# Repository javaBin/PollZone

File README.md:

# Arduino

Configure your Arduino IDE with ESP8266 support: File -> Preferences, add `http://arduino.esp8266.com/stable/package_esp8266com_index.json` under *Additional Board Manager URLs*.

Open the Board Manager: Tools -> Board -> Board Manager and add the `esp8266` board. Current version: `2.2.0`

# BOM - Bill of materials

For 20 bokser:

* 20 x grønn knapper
* 20 x gule knapper
* 20 x røde knapper
* 6 blanke PCBer
* loddetinn
* 20 NodeMCU 
* 20 usb-kabler (kanskje lange, spør hilde)
* 20 ladere
* 80 x distanseskruer 2-3mm
* 80 x maskinskruer til distanseskruer
* 20 x micro-usb-kontakter
* 60 x 1k ohm motstander
* 60 x 120 ohm til blå led
* 60 x 150 ohm til gul led
* 60 x 150 ohm til rød led
* 60 x kondensator
* 240 sko "ca størrelse 15"
* ledninger 

# TODOs

## Box

Modifiser trekasse.
- Litt lavere
- Skjære ut små hull for "feste-tapper" i led-lysene
- USB-utgang på sidevegg
- Gravere inn logo
- plexiglass/akryl
- 3d-printe mounting-brackets for usb.
- Huske å legg panelet riktig vei slik at "svidde kanter" hanver på innsiden.

Avklaringer:
- 2.4GHz nett i spektrum
- Spør om det er strøm ved bordene

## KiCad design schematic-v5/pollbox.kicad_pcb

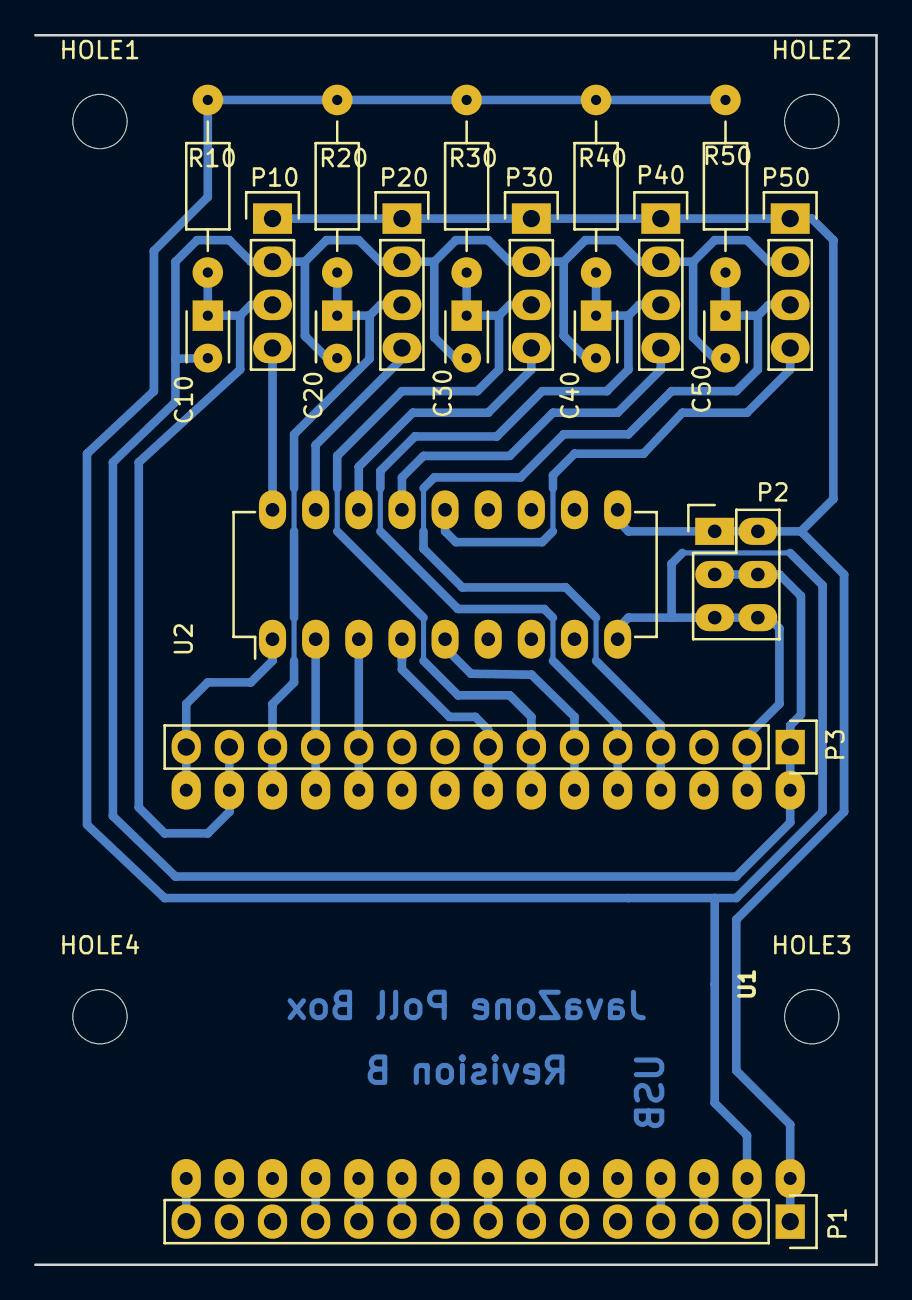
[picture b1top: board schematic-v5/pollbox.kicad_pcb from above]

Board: 2 copper layers, 49.5 x 72.4 mm, 24 parts (0 on the bottom side), 27 nets.

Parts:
C10, C20, C30, C40, C50: 100n; C_Disc_D3_P2.5
HOLE1: M1; MountingHole_3.2mm_M3
HOLE2: M2; MountingHole_3.2mm_M3
HOLE3: M4; MountingHole_3.2mm_M3
HOLE4: M3; MountingHole_3.2mm_M3
P1, P3: Pin_Header_Straight_1x15
P2: Power; Pin_Header_Straight_2x03
P10: SW_1; Pin_Header_Straight_1x04
P20: SW_2; Pin_Header_Straight_1x04
P30: SW_3; Pin_Header_Straight_1x04
P40: SW_4; Pin_Header_Straight_1x04
P50: SW_5; Pin_Header_Straight_1x04
R10, R20, R30, R40, R50: 10k; Resistor_Horizontal_RM10mm
U1: NodeMCU_1.0; NodeMCU
U2: ULN2803; DIP-18_W7.62mm_LongPads

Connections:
+3V3: C10.2, C20.2, C30.2, C40.2, C50.2, P2.3, P2.4, P3.1, P10.2, P20.2, P30.2, P40.2, P50.2, U1.30
+5V: P1.1, P2.1, P2.2, P10.1, P20.1, P30.1, P40.1, P50.1, U1.1, U2.10
/AD0: P1.15, U1.15
/CLK: P1.7, U1.7
/CMD: P1.9, U1.9
/EN: P1.4, U1.4
/LED_1: P3.15, U1.16, U2.1
/LED_1_OUT: P10.4, U2.18
/LED_2: P3.12, U1.19, U2.2
/LED_2_OUT: P20.4, U2.17
/LED_3: P3.11, U1.20, U2.3
/LED_3_OUT: P30.4, U2.16
/LED_4: P3.8, U1.23, U2.4
/LED_4_OUT: P40.4, U2.15
/LED_5: P3.6, U1.25, U2.5
/LED_5_OUT: P50.4, U2.14
/SD0: P1.8, U1.8
/SD1: P1.10, U1.10
/SD2: P1.11, U1.11
/SD3: P1.12, U1.12
/SWITCH_1: C10.1, P3.14, P10.3, R10.1, U1.17
/SWITCH_2: C20.1, P3.13, P20.3, R20.1, U1.18
/SWITCH_3: C30.1, P3.7, P30.3, R30.1, U1.24
/SWITCH_4: C40.1, P3.5, P40.3, R40.1, U1.26
/SWITCH_5: C50.1, P3.4, P50.3, R50.1, U1.27
/~RST: P1.3, U1.3
GND: P1.2, P2.5, P2.6, P3.2, R10.2, R20.2, R30.2, R40.2, R50.2, U1.2, U1.29, U2.9

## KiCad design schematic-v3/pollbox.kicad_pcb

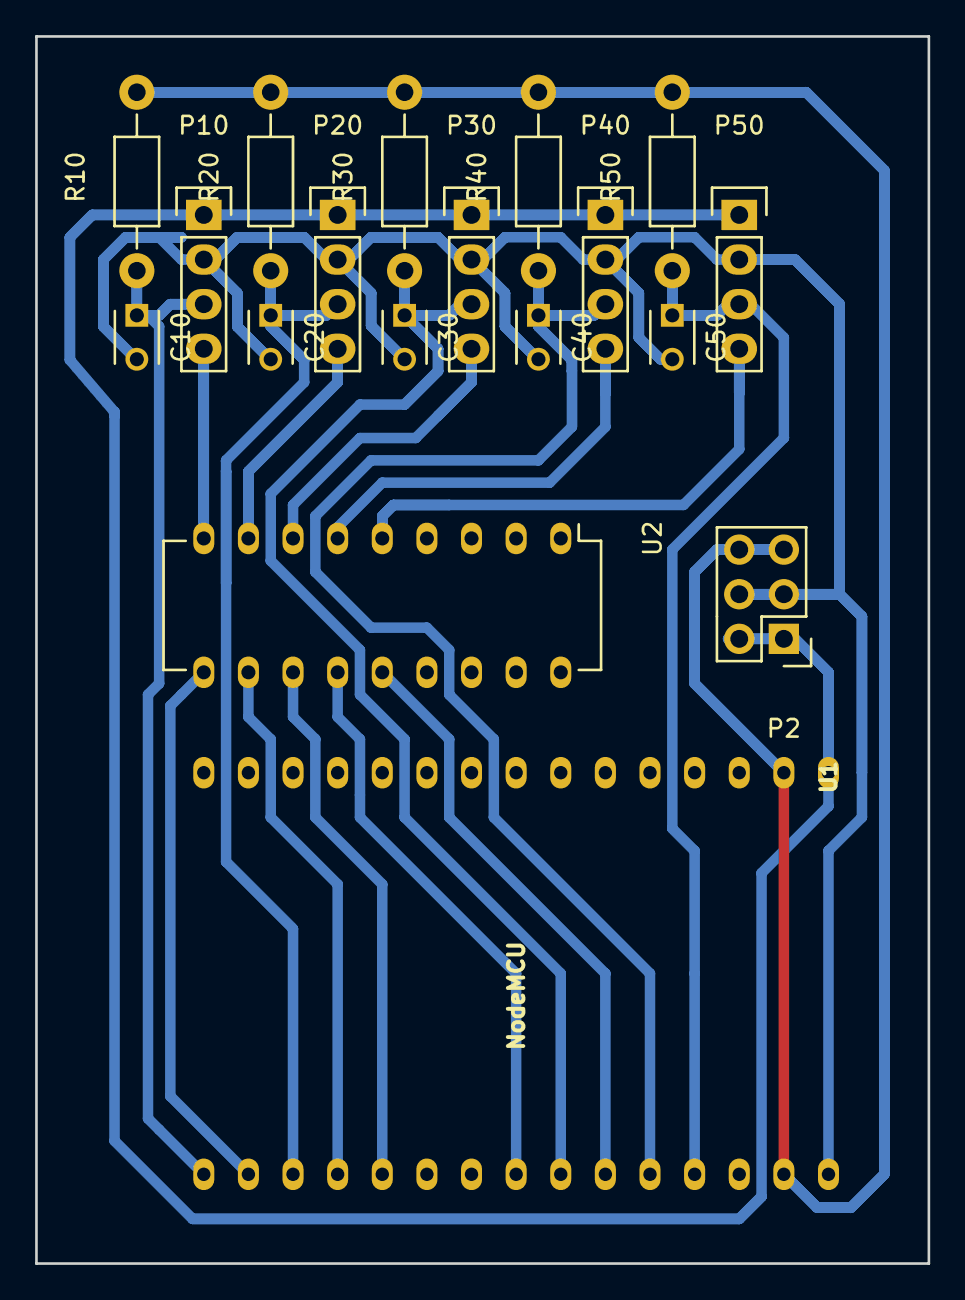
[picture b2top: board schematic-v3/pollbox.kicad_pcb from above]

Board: 2 copper layers, 50.8 x 69.8 mm, 18 parts (0 on the bottom side), 18 nets.

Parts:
C10, C20, C30, C40, C50: 100n; C_Disc_D3_P2.5
P2: CONN_02X03; Pin_Header_Straight_2x03
P10, P20, P30, P40, P50: CONN_01X04; Pin_Header_Straight_1x04
R10, R20, R30, R40, R50: 10k; Resistor_Horizontal_RM10mm
U1: NodeMCU; NodeMCU_oval_pads
U2: ULN2803; ULN2803_oval_pads

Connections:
+3V3: C10.2, C20.2, C30.2, C40.2, C50.2, P2.3, P2.4, P10.2, P20.2, P30.2, P40.2, P50.2, U1.30
+5V: P2.1, P2.2, P10.1, P20.1, P30.1, P40.1, P50.1, U1.1
/LED_1: P10.4, U2.9
/LED_2: P20.4, U2.8
/LED_3: P30.4, U2.7
/LED_4: P40.4, U2.6
/LED_5: P50.4, U2.5
/SWITCH_1: C10.1, P10.3, R10.1, U1.16
/SWITCH_2: C20.1, P20.3, R20.1, U1.18
/SWITCH_3: C30.1, P30.3, R30.1, U1.24
/SWITCH_4: C40.1, P40.3, R40.1, U1.26
/SWITCH_5: C50.1, P50.3, R50.1, U1.27
GND: P2.5, P2.6, R10.2, R20.2, R30.2, R40.2, R50.2, U1.2, U1.29
unnamed: U1.17, U2.10
unnamed: U1.19, U2.11
unnamed: U1.20, U2.12
unnamed: U1.23, U2.13
unnamed: U1.25, U2.14

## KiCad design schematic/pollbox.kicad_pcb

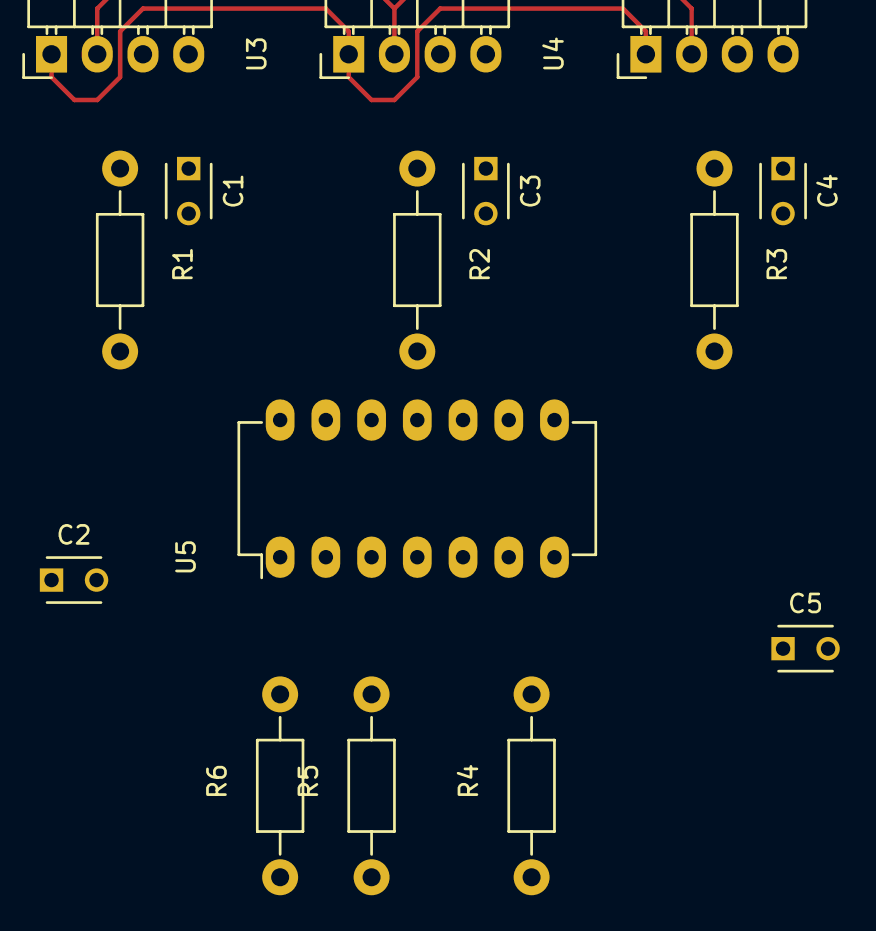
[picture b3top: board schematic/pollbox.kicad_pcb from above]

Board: 2 copper layers, 15 parts (0 on the bottom side), 12 nets.

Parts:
C1, C2, C3, C4, C5: 100n; C_Disc_D3_P2.5
R1, R2, R3: 10k; Resistor_Horizontal_RM10mm
R4, R5, R6: 1k; Resistor_Horizontal_RM10mm
U2, U3, U4: BIG_BUTTON; Pin_Header_Angled_1x04
U5: LM3046; DIP-14_W7.62mm_LongPads

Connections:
+3V3: C1.2, C3.2, C4.2, C5.2, U2.1, U3.1, U4.1
+5V: C2.1, U2.2, U3.2, U4.2
GND: C2.2, C5.1, R1.2, R2.2, R3.2, U5.7, U5.10, U5.13
unnamed: C1.1, R1.1, U2.4
unnamed: C3.1, R2.1, U3.4
unnamed: C4.1, R3.1, U4.4
unnamed: R4.2, U5.6
unnamed: R5.2, U5.9
unnamed: R6.2, U5.12
unnamed: U2.3, U5.14
unnamed: U3.3, U5.11
unnamed: U4.3, U5.8

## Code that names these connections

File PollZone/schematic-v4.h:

namespace schematic {

static const int AD0 = 0;
static const int LED_1 = 5;
static const int LED_2 = 0;
static const int LED_3 = 2;
static const int LED_4 = 14;
static const int LED_5 = 13;
static const int SD2 = 9;
static const int SD3 = 10;
static const int SWITCH_1 = 16;
static const int SWITCH_2 = 4;
static const int SWITCH_3 = 12;
static const int SWITCH_4 = 15;
static const int SWITCH_5 = 3;

} // namespace schematic

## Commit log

2015-12-01 o Adding schematic.
2015-12-01 added code for three buttons and reset button
2015-12-02 Added delay to compensate for poor debounce
2015-12-02 Included PubSubClient
2015-12-02 publishing to mqtt
2016-01-19 changed red in to D7 due to unstability issues
2016-01-23 Lagt til rotering av lys mens connecting til WiFi
2016-05-24 refactor: Moved source file to sub folder
    Arduino expects the main source file to be the same
    name as the folder. It's also case sensitive. To be
    able to name the git checkout folder to what we like
    we need to have the files in a sub folder in the git
    structure.
2016-05-24 style: Change coding style in PollZone.ino
2016-05-24 refactor: shrink PollZone file
    Split the PollZone into PollClient and PollButton. Remove the
    reset button and led control since it wasn't working as
    intended.
2016-05-24 feat: log status when connection to wifi
2016-05-24 fix: connect to mqtt server
    Connection to the mqtt server was lost in the
    refactroing. Adding it back again.
2016-05-24 fix: assign right variable in PollButton
2016-05-24 feat: disable led at setup for pollbutton
2016-05-24 fix: send event only on button release
2016-05-24 fix: ensure connection is up when sending data
    We don't need to keep the connection to the
    server up all the time. Only ensure that we
    have a connection when we need to send data.
2016-05-24 chore: remove experimental code
2016-05-25 fix: remove include fron PollZone.ino
2016-05-25 feat: process now return if the button is relased
    The goal is to remove the logic and copling to the
    client in the PollButton. This is the first step
    where we expose a flag to indecate if the button
    have registered a button release event.
2016-05-25 refactor: decopled button and client
    Now we're not sedning the push event inside
    the button class anymore. It's now moved to
    the state class.
2016-05-25 fix: reset counter to print status every 5 sec
    The counter wasn't reseted so we only printed the wifi
    status once.
2016-05-28 feat: remove persisting of messages
    We do not need the last message from the device
    to be stored on the mqtt broker.
2016-05-28 feat: Remove postfix / from topic
    It's not common to start the topic with a slash.
2016-05-28 feat: Send will message
2016-05-28 o Schematic with ULN2803.
2016-05-28 refactor: More c++ idiomatic code.
2016-05-29 fix: compile errors
2016-05-29 feat: change track width on pcb
2016-05-30 fix: retain should be true for online=true message
2016-08-04 o Schematic v4.
2016-08-04 o Support both widths of nodemcu boards. o Adding USB label for correct placement.
2016-08-04 o Filling zones. o Adding drill holes.
2016-08-04 o Selecting 'Small holes' when plotting.
2016-08-07 o Adding build setup to use kicad-utils to generate schematic-v4.h from the KiCAD schematic.
2016-08-09 o Adding dimmensions on layout.
2016-08-10 o Automatically generating plots with CMake.
2016-08-10 o Start of revision B board.
2016-08-11 o More TODOs.
2016-08-15 o Refreshing PDFs from updated CMake tools. o Cleaning up header and PDF generation for v4 and adding for v5 board.
2016-08-15 o Completing routing of board v5.
2016-08-17 rewire d0 and d1
    To enable interrupt on button
2016-08-17 cleanup some tracks
2016-08-17 bigger pads
2016-08-17 reduce islands
2016-08-17 fix conflict with mounting holes
2016-08-17 some more routes cleanup
2016-08-17 o Shrinking the board size so we can fit 2x2 on a single board when etching. o Fixing too large NodeMCU footprint. Double checking, yay!
2016-08-17 Add fixed 2x2 etching
2016-08-18 add missing wires
2016-08-18 fixed slik screen stuff
2016-08-18 more solder and silk mask stuff
2016-08-19 add gerber files
    Used for production at PCBWay
2016-08-22 o Removing default configuration and checking if it is set at compile time to prevent people from running without a configured build.
2016-08-22 o Reformatting.
2016-08-22 o Adding a Cfg class to contain the current configuration. Supports reading and writing the configuration. o Adding support for OTA (Over-the-air) uploading of firmware. o Adding support for reconfig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
2016-08-22 o Adjusting grid and aux origin so the print looks better.
2016-08-22 o FreeCAD model of box, revision 2.
2016-08-22 o Improved logo where the points actually meet each other.
2016-08-22 Fix compile errors
2016-08-22 Change led and button pins
2016-08-22 Stop subscribing for every button push
2016-08-24 Much improved model: o Fully modelling the buttons. o Adding a bounding box for the PCB to make sure that everything fits. o Adding mount holes for the PCB.
2016-08-24 o DXF and Auto Laser project files.
2016-08-25 o Correcting board placement holes.
2016-08-31 o Adding support for setting serial and name and OTP password. Serial can only be written once. o Publishing serial, namd and IP address.
2016-09-06 o Publishing build date + time as a version string.
2016-09-06 o Improved button leds, adding constant blinking
